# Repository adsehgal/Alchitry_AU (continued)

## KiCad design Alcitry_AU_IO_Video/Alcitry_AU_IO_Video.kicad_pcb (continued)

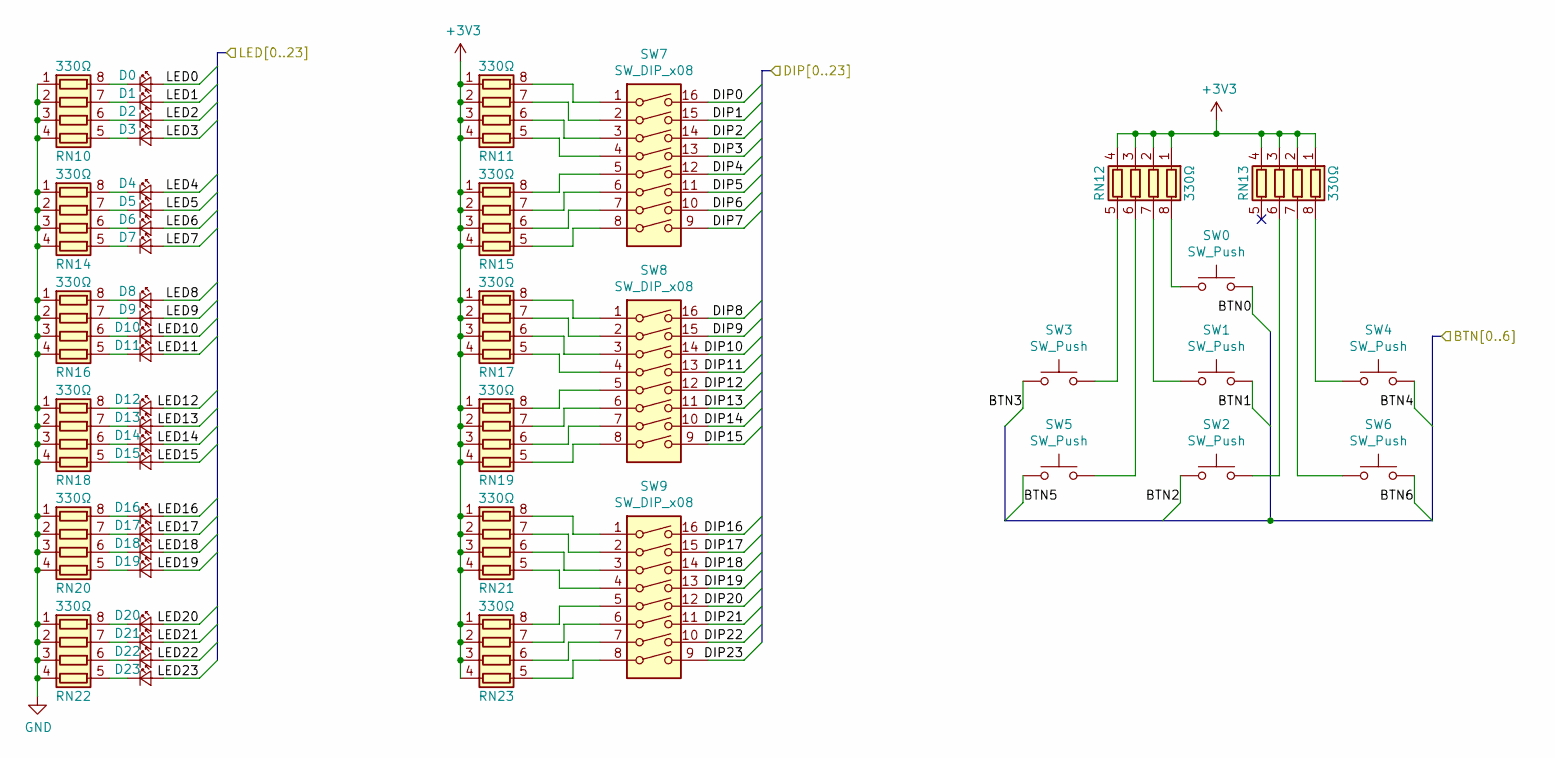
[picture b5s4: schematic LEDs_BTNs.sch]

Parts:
D0, D1, D2, D3, D4, D5, D6, D7, D8, D9, D10, D11, D12, D13, D14, D15, D16, D17, D18, D19, D20, D21, D22, D23: LED_Small; LED_0603_1608Metric_Pad1.05x0.95mm_HandSolder
RN10, RN11, RN12, RN13, RN14, RN15, RN16, RN17, RN18, RN19, RN20, RN21, RN22, RN23: 330Ω; R_Array_Convex_4x0603
SW0, SW1, SW2, SW3, SW4, SW5, SW6: SW_Push; SW_SPST_TL3342
SW7, SW8, SW9: SW_DIP_x08; SW_DIP_SPSTx08_Slide_Omron_A6H-8101_W6.15mm_P1.27mm

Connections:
+3V3: RN11.1 (R1.1), RN11.2 (R2.1), RN11.3 (R3.1), RN11.4 (R4.1), RN12.1 (R1.1), RN12.2 (R2.1), RN12.3 (R3.1), RN12.4 (R4.1), RN13.1 (R1.1), RN13.2 (R2.1), RN13.3 (R3.1), RN13.4 (R4.1), RN15.1 (R1.1), RN15.2 (R2.1), RN15.3 (R3.1), RN15.4 (R4.1), RN17.1 (R1.1), RN17.2 (R2.1), RN17.3 (R3.1), RN17.4 (R4.1), RN19.1 (R1.1), RN19.2 (R2.1), RN19.3 (R3.1), RN19.4 (R4.1), RN21.1 (R1.1), RN21.2 (R2.1), RN21.3 (R3.1), RN21.4 (R4.1), RN23.1 (R1.1), RN23.2 (R2.1), RN23.3 (R3.1), RN23.4 (R4.1); also elsewhere on the board
/BTN0: SW0.1; also elsewhere on the board
/BTN1: SW1.1; also elsewhere on the board
/BTN2: SW2.1; also elsewhere on the board
/BTN3: SW3.1; also elsewhere on the board
/BTN4: SW4.1; also elsewhere on the board
/BTN5: SW5.1; also elsewhere on the board
/BTN6: SW6.1; also elsewhere on the board
/DIP0: SW7.16; also elsewhere on the board
/DIP1: SW7.15; also elsewhere on the board
/DIP2: SW7.14; also elsewhere on the board
/DIP3: SW7.13; also elsewhere on the board
/DIP4: SW7.12; also elsewhere on the board
/DIP5: SW7.11; also elsewhere on the board
/DIP6: SW7.10; also elsewhere on the board
/DIP7: SW7.9; also elsewhere on the board
/DIP8: SW8.16; also elsewhere on the board
/DIP9: SW8.15; also elsewhere on the board
/DIP10: SW8.14; also elsewhere on the board
/DIP11: SW8.13; also elsewhere on the board
/DIP12: SW8.12; also elsewhere on the board
/DIP13: SW8.11; also elsewhere on the board
/DIP14: SW8.10; also elsewhere on the board
/DIP15: SW8.9; also elsewhere on the board
/DIP16: SW9.16; also elsewhere on the board
/DIP17: SW9.15; also elsewhere on the board
/DIP18: SW9.14; also elsewhere on the board
/DIP19: SW9.13; also elsewhere on the board
/DIP20: SW9.12; also elsewhere on the board
/DIP21: SW9.11; also elsewhere on the board
/DIP22: SW9.10; also elsewhere on the board
/DIP23: SW9.9; also elsewhere on the board
/LED0: D0.2 (A); also elsewhere on the board
/LED1: D1.2 (A); also elsewhere on the board
/LED2: D2.2 (A); also elsewhere on the board
/LED3: D3.2 (A); also elsewhere on the board
/LED4: D4.2 (A); also elsewhere on the board
/LED5: D5.2 (A); also elsewhere on the board
/LED6: D6.2 (A); also elsewhere on the board
/LED7: D7.2 (A); also elsewhere on the board
/LED8: D8.2 (A); also elsewhere on the board
/LED9: D9.2 (A); also elsewhere on the board
/LED10: D10.2 (A); also elsewhere on the board
/LED11: D11.2 (A); also elsewhere on the board
/LED12: D12.2 (A); also elsewhere on the board
/LED13: D13.2 (A); also elsewhere on the board
/LED14: D14.2 (A); also elsewhere on the board
/LED15: D15.2 (A); also elsewhere on the board
/LED16: D16.2 (A); also elsewhere on the board
/LED17: D17.2 (A); also elsewhere on the board
/LED18: D18.2 (A); also elsewhere on the board
/LED19: D19.2 (A); also elsewhere on the board
/LED20: D20.2 (A); also elsewhere on the board
/LED21: D21.2 (A); also elsewhere on the board
/LED22: D22.2 (A); also elsewhere on the board
/LED23: D23.2 (A); also elsewhere on the board
GND: RN10.1 (R1.1), RN10.2 (R2.1), RN10.3 (R3.1), RN10.4 (R4.1), RN14.1 (R1.1), RN14.2 (R2.1), RN14.3 (R3.1), RN14.4 (R4.1), RN16.1 (R1.1), RN16.2 (R2.1), RN16.3 (R3.1), RN16.4 (R4.1), RN18.1 (R1.1), RN18.2 (R2.1), RN18.3 (R3.1), RN18.4 (R4.1), RN20.1 (R1.1), RN20.2 (R2.1), RN20.3 (R3.1), RN20.4 (R4.1), RN22.1 (R1.1), RN22.2 (R2.1), RN22.3 (R3.1), RN22.4 (R4.1)
unnamed: D0.1 (K), RN10.8 (R1.2)
unnamed: D1.1 (K), RN10.7 (R2.2)
unnamed: D2.1 (K), RN10.6 (R3.2)
unnamed: D3.1 (K), RN10.5 (R4.2)
unnamed: D4.1 (K), RN14.8 (R1.2)
unnamed: D5.1 (K), RN14.7 (R2.2)
unnamed: D6.1 (K), RN14.6 (R3.2)
unnamed: D7.1 (K), RN14.5 (R4.2)
unnamed: D8.1 (K), RN16.8 (R1.2)
unnamed: D9.1 (K), RN16.7 (R2.2)
unnamed: D10.1 (K), RN16.6 (R3.2)
unnamed: D11.1 (K), RN16.5 (R4.2)
unnamed: D12.1 (K), RN18.8 (R1.2)
unnamed: D13.1 (K), RN18.7 (R2.2)
unnamed: D14.1 (K), RN18.6 (R3.2)
unnamed: D15.1 (K), RN18.5 (R4.2)
unnamed: D16.1 (K), RN20.8 (R1.2)
unnamed: D17.1 (K), RN20.7 (R2.2)
unnamed: D18.1 (K), RN20.6 (R3.2)
unnamed: D19.1 (K), RN20.5 (R4.2)
unnamed: D20.1 (K), RN22.8 (R1.2)
unnamed: D21.1 (K), RN22.7 (R2.2)
unnamed: D22.1 (K), RN22.6 (R3.2)
unnamed: D23.1 (K), RN22.5 (R4.2)
unnamed: RN11.5 (R4.2), SW7.4
unnamed: RN11.6 (R3.2), SW7.3
unnamed: RN11.7 (R2.2), SW7.2
unnamed: RN11.8 (R1.2), SW7.1
unnamed: RN12.5 (R4.2), SW3.2
unnamed: RN12.6 (R3.2), SW5.2
unnamed: RN12.7 (R2.2), SW1.2
unnamed: RN12.8 (R1.2), SW0.2
unnamed: RN13.6 (R3.2), SW2.2
unnamed: RN13.7 (R2.2), SW6.2
unnamed: RN13.8 (R1.2), SW4.2
unnamed: RN15.5 (R4.2), SW7.8
unnamed: RN15.6 (R3.2), SW7.7
unnamed: RN15.7 (R2.2), SW7.6
unnamed: RN15.8 (R1.2), SW7.5
unnamed: RN17.5 (R4.2), SW8.4
unnamed: RN17.6 (R3.2), SW8.3
unnamed: RN17.7 (R2.2), SW8.2
unnamed: RN17.8 (R1.2), SW8.1
unnamed: RN19.5 (R4.2), SW8.8
unnamed: RN19.6 (R3.2), SW8.7
unnamed: RN19.7 (R2.2), SW8.6
unnamed: RN19.8 (R1.2), SW8.5
unnamed: RN21.5 (R4.2), SW9.4
unnamed: RN21.6 (R3.2), SW9.3
unnamed: RN21.7 (R2.2), SW9.2
unnamed: RN21.8 (R1.2), SW9.1
unnamed: RN23.5 (R4.2), SW9.8
unnamed: RN23.6 (R3.2), SW9.7
unnamed: RN23.7 (R2.2), SW9.6
unnamed: RN23.8 (R1.2), SW9.5

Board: 2 copper layers, 90 parts (16 on the bottom side), 201 nets, no tracks yet.

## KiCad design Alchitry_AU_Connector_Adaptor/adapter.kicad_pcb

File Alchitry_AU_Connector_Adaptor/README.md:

# Alchitry_AU_Adaptor
Adaptor designed to convert the Alchitry AU 0.5mm pitch connectors to a more manageable 1mm pitch connectors offered by Harwin.

Goal of this adaptor is to make breakout boards much easier to solder once the adaptor is in place.

Harwin Connectors:

Female: M55-7005042R

      https://www.digikey.com/product-detail/en/harwin-inc/M55-7005042R/952-3872-1-ND/8537656
      
Male: M55-6005042R

      https://www.digikey.com/product-detail/en/harwin-inc/M55-6005042R/952-3840-1-ND/8537624

The prototype boards were fabricated by JLCPCB.

EDA tool used: KiCad

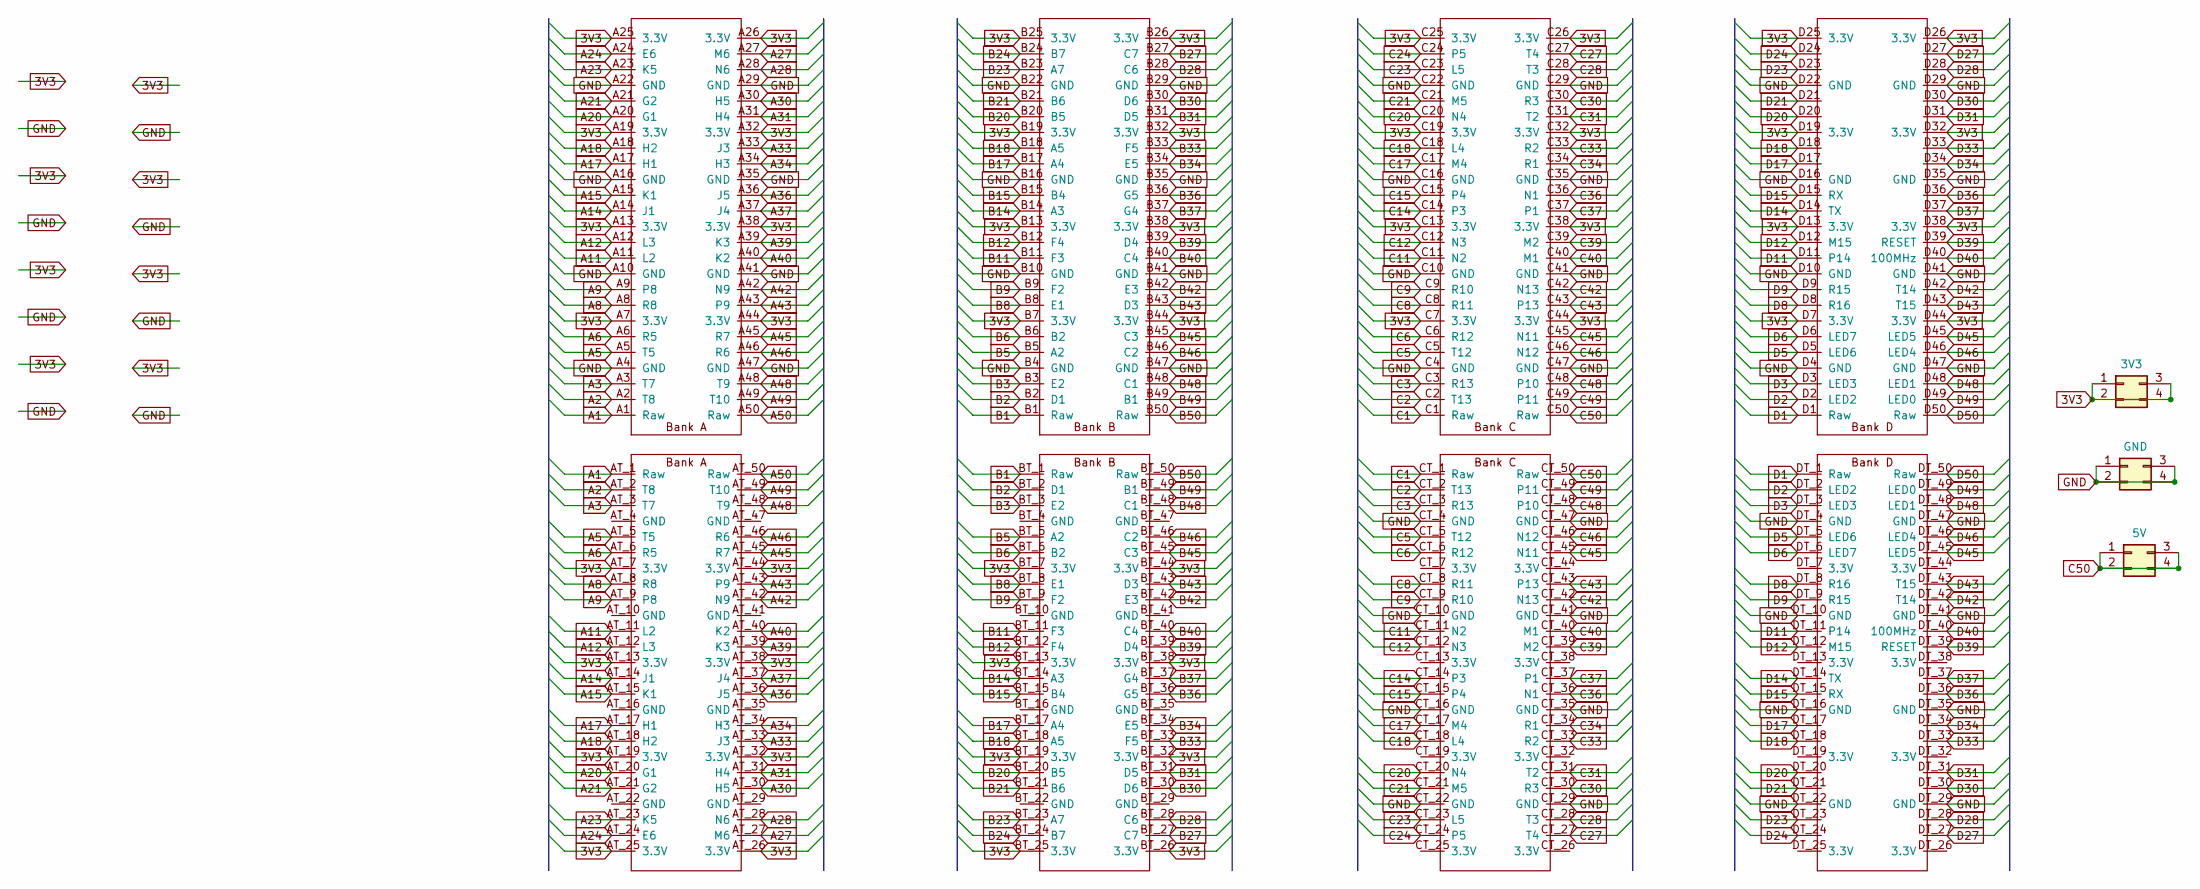
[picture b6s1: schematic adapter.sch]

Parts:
J1: 3V3; PinHeader_2x02_P2.54mm_Vertical
J2: GND; PinHeader_2x02_P2.54mm_Vertical
J3: 5V; PinHeader_2x02_P2.54mm_Vertical
U1: ADAPTOR_TOPX4; Alchitry_board_ADAPTOR_TOP

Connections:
3V3: J1.1, J1.2, J1.3, J1.4, U1.A7 (3.3V), U1.A13 (3.3V), U1.A19 (3.3V), U1.A25 (3.3V), U1.A26 (3.3V), U1.A32 (3.3V), U1.A38 (3.3V), U1.A44 (3.3V), U1.AT_7 (3.3V), U1.AT_13 (3.3V), U1.AT_19 (3.3V), U1.AT_25 (3.3V), U1.AT_26 (3.3V), U1.AT_32 (3.3V), U1.AT_38 (3.3V), U1.AT_44 (3.3V), U1.B7 (3.3V), U1.B13 (3.3V), U1.B19 (3.3V), U1.B25 (3.3V), U1.B26 (3.3V), U1.B32 (3.3V), U1.B38 (3.3V), U1.B44 (3.3V), U1.BT_7 (3.3V), U1.BT_13 (3.3V), U1.BT_19 (3.3V), U1.BT_25 (3.3V), U1.BT_26 (3.3V), U1.BT_32 (3.3V), U1.BT_38 (3.3V), U1.BT_44 (3.3V), U1.C7 (3.3V), U1.C13 (3.3V), U1.C19 (3.3V), U1.C25 (3.3V), U1.C26 (3.3V), U1.C32 (3.3V), U1.C38 (3.3V), U1.C44 (3.3V), U1.D7 (3.3V), U1.D13 (3.3V), U1.D19 (3.3V), U1.D25 (3.3V), U1.D26 (3.3V), U1.D32 (3.3V), U1.D38 (3.3V), U1.D44 (3.3V)
A1: U1.A1 (Raw), U1.AT_1 (Raw)
A2: U1.A2 (T8), U1.AT_2 (T8)
A3: U1.A3 (T7), U1.AT_3 (T7)
A5: U1.A5 (T5), U1.AT_5 (T5)
A6: U1.A6 (R5), U1.AT_6 (R5)
A8: U1.A8 (R8), U1.AT_8 (R8)
A9: U1.A9 (P8), U1.AT_9 (P8)
A11: U1.A11 (L2), U1.AT_11 (L2)
A12: U1.A12 (L3), U1.AT_12 (L3)
A14: U1.A14 (J1), U1.AT_14 (J1)
A15: U1.A15 (K1), U1.AT_15 (K1)
A17: U1.A17 (H1), U1.AT_17 (H1)
A18: U1.A18 (H2), U1.AT_18 (H2)
A20: U1.A20 (G1), U1.AT_20 (G1)
A21: U1.A21 (G2), U1.AT_21 (G2)
A23: U1.A23 (K5), U1.AT_23 (K5)
A24: U1.A24 (E6), U1.AT_24 (E6)
A27: U1.A27 (M6), U1.AT_27 (M6)
A28: U1.A28 (N6), U1.AT_28 (N6)
A30: U1.A30 (H5), U1.AT_30 (H5)
A31: U1.A31 (H4), U1.AT_31 (H4)
A33: U1.A33 (J3), U1.AT_33 (J3)
A34: U1.A34 (H3), U1.AT_34 (H3)
A36: U1.A36 (J5), U1.AT_36 (J5)
A37: U1.A37 (J4), U1.AT_37 (J4)
A39: U1.A39 (K3), U1.AT_39 (K3)
A40: U1.A40 (K2), U1.AT_40 (K2)
A42: U1.A42 (N9), U1.AT_42 (N9)
A43: U1.A43 (P9), U1.AT_43 (P9)
A45: U1.A45 (R7), U1.AT_45 (R7)
A46: U1.A46 (R6), U1.AT_46 (R6)
A48: U1.A48 (T9), U1.AT_48 (T9)
A49: U1.A49 (T10), U1.AT_49 (T10)
A50: U1.A50 (Raw), U1.AT_50 (Raw)
B1: U1.B1 (Raw), U1.BT_1 (Raw)
B2: U1.B2 (D1), U1.BT_2 (D1)
B3: U1.B3 (E2), U1.BT_3 (E2)
B5: U1.B5 (A2), U1.BT_5 (A2)
B6: U1.B6 (B2), U1.BT_6 (B2)
B8: U1.B8 (E1), U1.BT_8 (E1)
B9: U1.B9 (F2), U1.BT_9 (F2)
B11: U1.B11 (F3), U1.BT_11 (F3)
B12: U1.B12 (F4), U1.BT_12 (F4)
B14: U1.B14 (A3), U1.BT_14 (A3)
B15: U1.B15 (B4), U1.BT_15 (B4)
B17: U1.B17 (A4), U1.BT_17 (A4)
B18: U1.B18 (A5), U1.BT_18 (A5)
B20: U1.B20 (B5), U1.BT_20 (B5)
B21: U1.B21 (B6), U1.BT_21 (B6)
B23: U1.B23 (A7), U1.BT_23 (A7)
B24: U1.B24 (B7), U1.BT_24 (B7)
B27: U1.B27 (C7), U1.BT_27 (C7)
B28: U1.B28 (C6), U1.BT_28 (C6)
B30: U1.B30 (D6), U1.BT_30 (D6)
B31: U1.B31 (D5), U1.BT_31 (D5)
B33: U1.B33 (F5), U1.BT_33 (F5)
B34: U1.B34 (E5), U1.BT_34 (E5)
B36: U1.B36 (G5), U1.BT_36 (G5)
B37: U1.B37 (G4), U1.BT_37 (G4)
B39: U1.B39 (D4), U1.BT_39 (D4)
B40: U1.B40 (C4), U1.BT_40 (C4)
B42: U1.B42 (E3), U1.BT_42 (E3)
B43: U1.B43 (D3), U1.BT_43 (D3)
B45: U1.B45 (C3), U1.BT_45 (C3)
B46: U1.B46 (C2), U1.BT_46 (C2)
B48: U1.B48 (C1), U1.BT_48 (C1)
B49: U1.B49 (B1), U1.BT_49 (B1)
B50: U1.B50 (Raw), U1.BT_50 (Raw)
C1: U1.C1 (Raw), U1.CT_1 (Raw)
C2: U1.C2 (T13), U1.CT_2 (T13)
C3: U1.C3 (R13), U1.CT_3 (R13)
C5: U1.C5 (T12), U1.CT_5 (T12)
C6: U1.C6 (R12), U1.CT_6 (R12)
C8: U1.C8 (R11), U1.CT_8 (R11)
C9: U1.C9 (R10), U1.CT_9 (R10)
C11: U1.C11 (N2), U1.CT_11 (N2)
C12: U1.C12 (N3), U1.CT_12 (N3)
C14: U1.C14 (P3), U1.CT_14 (P3)
C15: U1.C15 (P4), U1.CT_15 (P4)
C17: U1.C17 (M4), U1.CT_17 (M4)
C18: U1.C18 (L4), U1.CT_18 (L4)
C20: U1.C20 (N4), U1.CT_20 (N4)
C21: U1.C21 (M5), U1.CT_21 (M5)
C23: U1.C23 (L5), U1.CT_23 (L5)
C24: U1.C24 (P5), U1.CT_24 (P5)
C27: U1.C27 (T4), U1.CT_27 (T4)
C28: U1.C28 (T3), U1.CT_28 (T3)
C30: U1.C30 (R3), U1.CT_30 (R3)
C31: U1.C31 (T2), U1.CT_31 (T2)
C33: U1.C33 (R2), U1.CT_33 (R2)
C34: U1.C34 (R1), U1.CT_34 (R1)
C36: U1.C36 (N1), U1.CT_36 (N1)
C37: U1.C37 (P1), U1.CT_37 (P1)
C39: U1.C39 (M2), U1.CT_39 (M2)
C40: U1.C40 (M1), U1.CT_40 (M1)
C42: U1.C42 (N13), U1.CT_42 (N13)
C43: U1.C43 (P13), U1.CT_43 (P13)
C45: U1.C45 (N11), U1.CT_45 (N11)
C46: U1.C46 (N12), U1.CT_46 (N12)
C48: U1.C48 (P10), U1.CT_48 (P10)
C49: U1.C49 (P11), U1.CT_49 (P11)
C50: J3.1, J3.2, J3.3, J3.4, U1.C50 (Raw), U1.CT_50 (Raw)
D1: U1.D1 (Raw), U1.DT_1 (Raw)
D2: U1.D2 (LED2), U1.DT_2 (LED2)
D3: U1.D3 (LED3), U1.DT_3 (LED3)
D5: U1.D5 (LED6), U1.DT_5 (LED6)
D6: U1.D6 (LED7), U1.DT_6 (LED7)
D8: U1.D8 (R16), U1.DT_8 (R16)
D9: U1.D9 (R15), U1.DT_9 (R15)
D11: U1.D11 (P14), U1.DT_11 (P14)
D12: U1.D12 (M15), U1.DT_12 (M15)
D14: U1.D14 (TX), U1.DT_14 (TX)
D15: U1.D15 (RX), U1.DT_15 (RX)
D17: U1.D17, U1.DT_17
D18: U1.D18, U1.DT_18
D20: U1.D20, U1.DT_20
D21: U1.D21, U1.DT_21
D23: U1.D23, U1.DT_23
D24: U1.D24, U1.DT_24
D27: U1.D27, U1.DT_27
D28: U1.D28, U1.DT_28
D30: U1.D30, U1.DT_30
D31: U1.D31, U1.DT_31
D33: U1.D33, U1.DT_33
D34: U1.D34, U1.DT_34
D36: U1.D36, U1.DT_36
D37: U1.D37, U1.DT_37
D39: U1.D39 (RESET), U1.DT_39 (RESET)
D40: U1.D40 (100MHz), U1.DT_40 (100MHz)
D42: U1.D42 (T14), U1.DT_42 (T14)
D43: U1.D43 (T15), U1.DT_43 (T15)
D45: U1.D45 (LED5), U1.DT_45 (LED5)
D46: U1.D46 (LED4), U1.DT_46 (LED4)
D48: U1.D48 (LED1), U1.DT_48 (LED1)
D49: U1.D49 (LED0), U1.DT_49 (LED0)
D50: U1.D50 (Raw), U1.DT_50 (Raw)
GND: J2.1, J2.2, J2.3, J2.4, U1.A4 (GND), U1.A10 (GND), U1.A16 (GND), U1.A22 (GND), U1.A29 (GND), U1.A35 (GND), U1.A41 (GND), U1.A47 (GND), U1.B4 (GND), U1.B10 (GND), U1.B16 (GND), U1.B22 (GND), U1.B29 (GND), U1.B35 (GND), U1.B41 (GND), U1.B47 (GND), U1.C4 (GND), U1.C10 (GND), U1.C16 (GND), U1.C22 (GND), U1.C29 (GND), U1.C35 (GND), U1.C41 (GND), U1.C47 (GND), U1.CT_4 (GND), U1.CT_10 (GND), U1.CT_16 (GND), U1.CT_22 (GND), U1.CT_29 (GND), U1.CT_35 (GND), U1.CT_41 (GND), U1.CT_47 (GND), U1.D4 (GND), U1.D10 (GND), U1.D16 (GND), U1.D22 (GND), U1.D29 (GND), U1.D35 (GND), U1.D41 (GND), U1.D47 (GND), U1.DT_4 (GND), U1.DT_10 (GND), U1.DT_16 (GND), U1.DT_22 (GND), U1.DT_29 (GND), U1.DT_35 (GND), U1.DT_41 (GND), U1.DT_47 (GND)

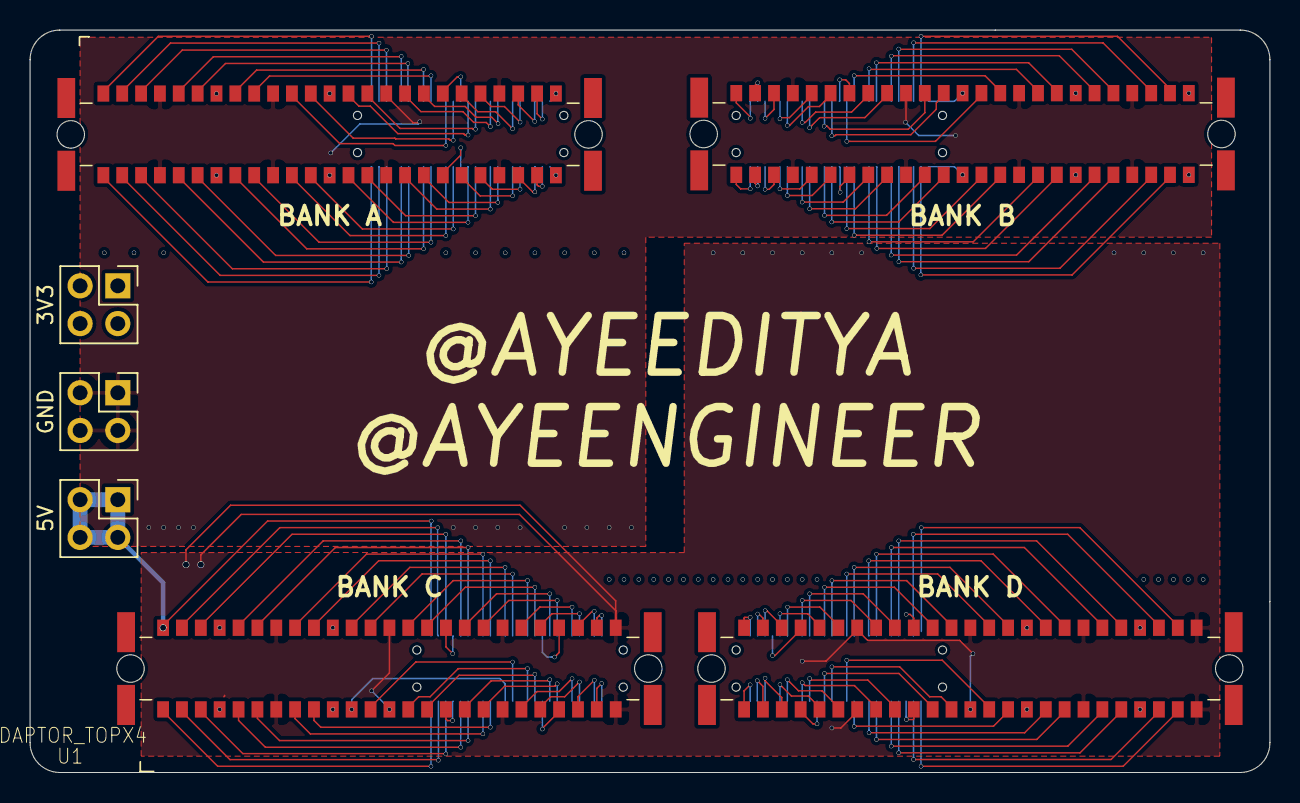
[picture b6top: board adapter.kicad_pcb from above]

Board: 2 copper layers, 83.5 x 50.0 mm, 4 parts (0 on the bottom side), 138 nets.

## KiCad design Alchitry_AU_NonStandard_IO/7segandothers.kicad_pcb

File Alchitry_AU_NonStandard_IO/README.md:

# Alchitry_AU_BreakoutV2
Breakout Board designed to be used with the Alchitry AU FPGA in conjunction with the mezzanine adaptor dersigned by me.
The breakout board has 5x tacticle buttons, 8x LEDs, 4x DIP switches, 2x 2-Digit 7 segment displays, extra breakout pins from Bank B as well as pin headers for the HDMI adaptor designed by 1bit-squared.

Goal of this breakout board is to offer similar functionality as the one offered by Alchitry in addition to HDMI output and extra headers if needed.

Note: the HDMI headers can be used as regular I/O as well.

HDMI Adaptor:

https://1bitsquared.com/products/pmod-digital-video-interface?variant=11770730020911&currency=USD&gclid=Cj0KCQjwov3nBRDFARIsANgsdoHOZecOSm0TIER7f1FJA3ifWDU8KhmRx257o6HcA4yRRT3OkXDNP8oaArPeEALw_wcB

DIP Switch:

https://lcsc.com/product-detail/DIP-Switches_Cixi-Tonver-Elec-Cixi-Tonver-Elec-HAD-04H-R_C3693.html

LEDs:

https://lcsc.com/product-detail/Light-Emitting-Diodes-LED_0805-blue_C205441.html

Tactile Buttons:

https://lcsc.com/product-detail/Tactile-Switches_Korean-Hroparts-Elec-K2-1187SQ-A4SW-06_C92584.html

7 Segment Displays:

https://lcsc.com/product-detail/Led-Segment-Display_SUNLIGHT-SLS0392FB4A1GD_C226000.html

Pull Down Resistors:

https://lcsc.com/product-detail/New-Arrivals_SANYEAR-SYLE0805JN330RP_C385915.html

Harwin Connectors:

Female: M55-7005042R

  https://www.digikey.com/product-detail/en/harwin-inc/M55-7005042R/952-3872-1-ND/8537656
Male: M55-6005042R

  https://www.digikey.com/product-detail/en/harwin-inc/M55-6005042R/952-3840-1-ND/8537624
  
The prototype boards were fabricated by JLCPCB.

EDA tool used: KiCad

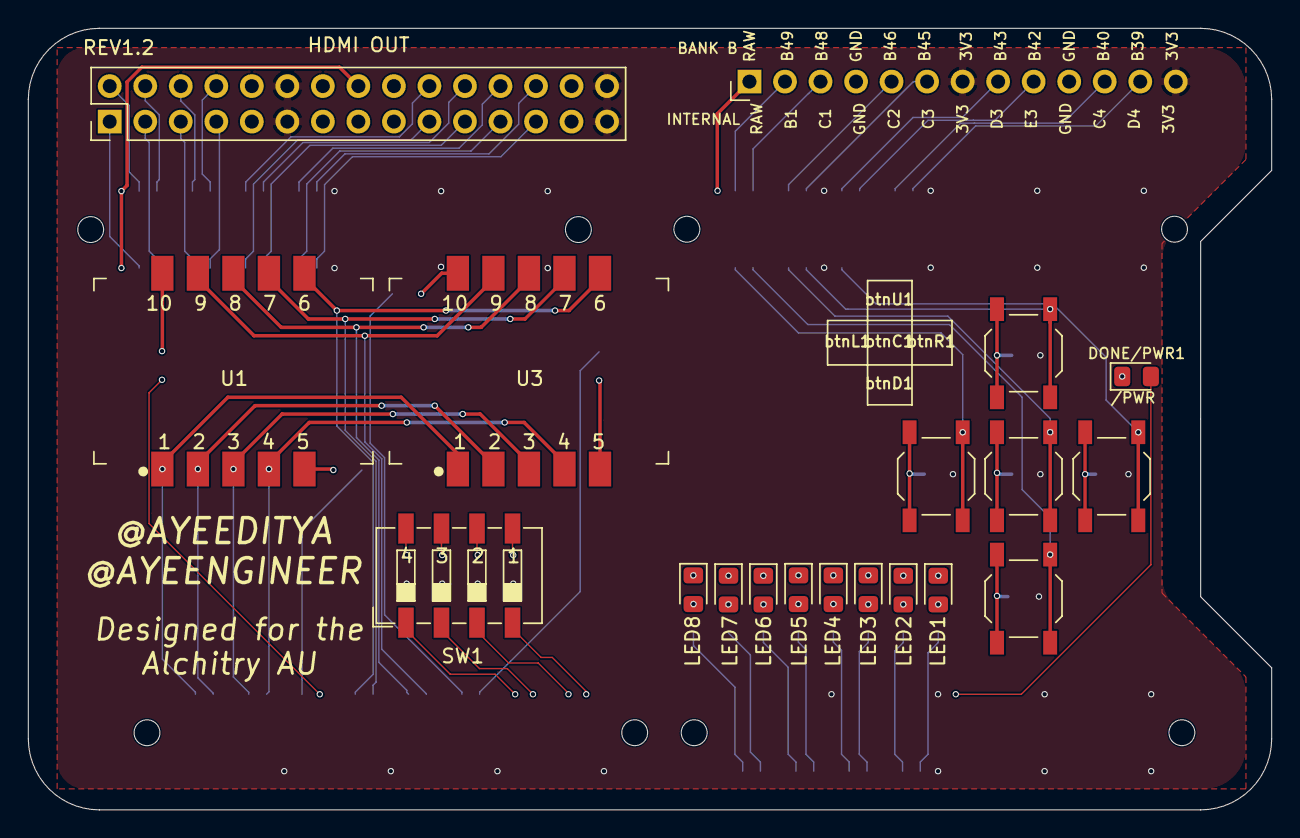
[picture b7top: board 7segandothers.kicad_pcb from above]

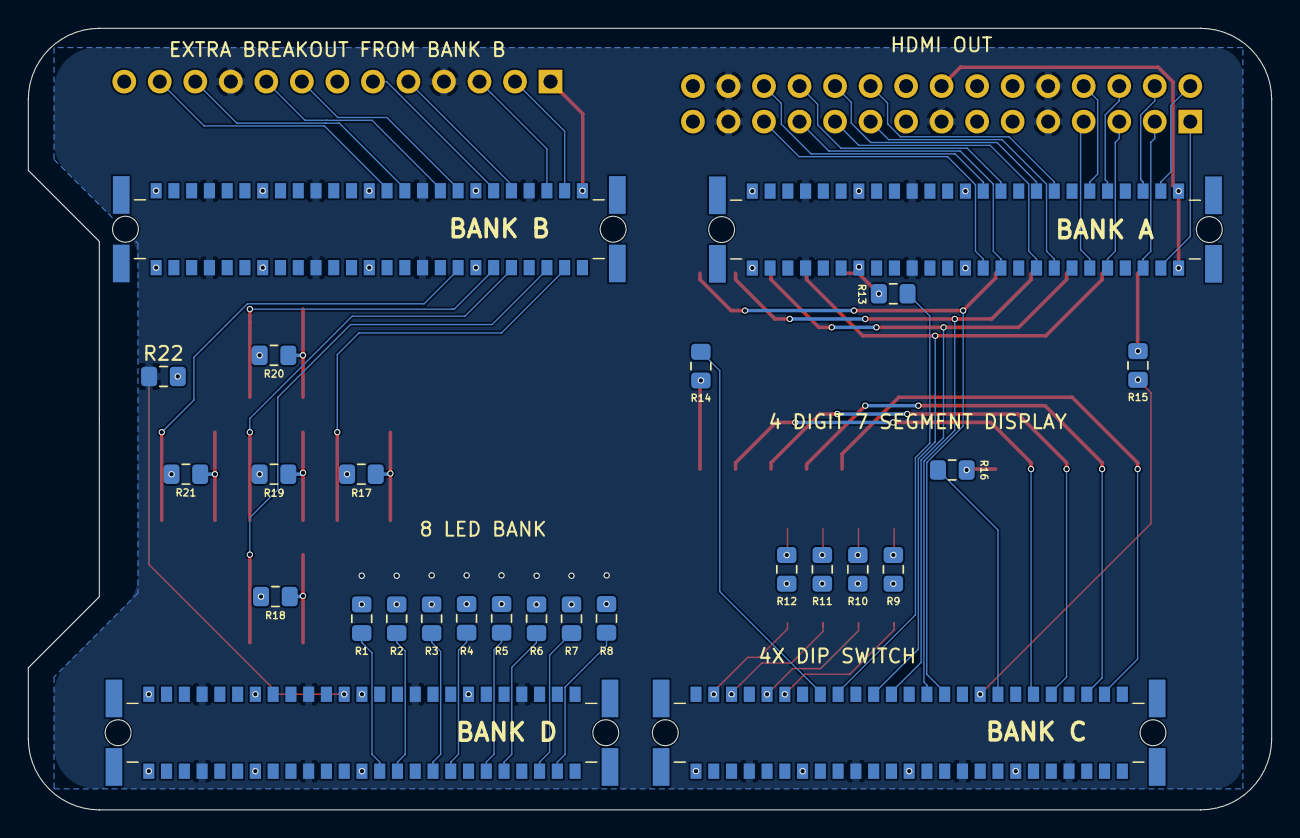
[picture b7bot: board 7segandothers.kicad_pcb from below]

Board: 2 copper layers, 88.9 x 55.9 mm, 42 parts (22 on the bottom side), 80 nets.

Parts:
DONE/PWR1: LED; LED_0805_2012Metric_Pad1.15x1.40mm_HandSolder
J1: Conn_02x15_Counter_Clockwise; PinHeader_2x15_P2.54mm_Vertical
J2: Conn_01x13_Male; PinHeader_1x13_P2.54mm_Vertical
LED1, LED2, LED3, LED4, LED5, LED6, LED7, LED8: LED; LED_0805_2012Metric_Pad1.15x1.40mm_HandSolder
R1, R2, R3, R4, R5, R6, R7, R8, R9, R10, R11, R12, R13, R14, R15, R16, R17, R18, R19, R20, R21, R22: R_Small_US; R_0805_2012Metric_Pad1.15x1.40mm_HandSolder
SW1: SW_DIP_x04; SW_DIP_SPSTx04_Slide_6.7x11.72mm_W6.73mm_P2.54mm_LowProfile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
U1, U3: smd_7seg_2dig_SLS0392FB4A1GD
U2: boardmezzanine_new; Alchitry_board_adapter_btm
btnC1: SW_Push_Dual; SW_SPST_TL3342
btnD1: SW_Push_Dual; SW_SPST_TL3342
btnL1: SW_Push_Dual; SW_SPST_TL3342
btnR1: SW_Push_Dual; SW_SPST_TL3342
btnU1: SW_Push_Dual; SW_SPST_TL3342

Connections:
B0: J1.19, U2.A40
B1: J1.11, U2.A9
B2: J1.10, U2.A8
B3: J1.21, U2.A43
CK: J1.20, U2.A42
DE: J1.12, U2.A11
G0: J1.4, U2.A6
G1: J1.27, U2.A45
G2: J1.3, U2.A5
G3: J1.28, U2.A46
GNDREF: J1.5, J1.8, J1.14, J1.17, J1.26, J2.4, J2.10, LED1.1, LED2.1, LED3.1, LED4.1, LED5.1, LED6.1, LED7.1, LED8.1, R22.1, U2.A16, U2.A22, U2.A29, U2.A35, U2.B10, U2.B16, U2.B22, U2.B29, U2.B35, U2.B41, U2.B47, U2.C4, U2.C10, U2.C16, U2.C22, U2.D16, U2.D22, U2.D29, U2.D35, U2.D41, U2.D47
HS: J1.18, U2.A39
unnamed: DONE/PWR1.1, R22.2
unnamed: DONE/PWR1.2, U2.D37
unnamed: J2.1, U2.B50
unnamed: J2.2, U2.B49
unnamed: J2.3, U2.B48
unnamed: J2.5, U2.B46
unnamed: J2.6, U2.B45
unnamed: J2.8, U2.B43
unnamed: J2.9, U2.B42
unnamed: J2.11, U2.B40
unnamed: J2.12, U2.B39
unnamed: LED1.2, R1.1
unnamed: LED2.2, R2.1
unnamed: LED3.2, R3.1
unnamed: LED4.2, R4.1
unnamed: LED5.2, R5.1
unnamed: LED6.2, R6.1
unnamed: LED7.2, R7.1
unnamed: LED8.2, R8.1
unnamed: R1.2, U2.D12
unnamed: R2.2, U2.D11
unnamed: R3.2, U2.D9
unnamed: R4.2, U2.D8
unnamed: R5.2, U2.D6
unnamed: R6.2, U2.D5
unnamed: R7.2, U2.D3
unnamed: R8.2, U2.D2
unnamed: R9.2, SW1.8
unnamed: R10.2, SW1.7
unnamed: R11.2, SW1.6
unnamed: R12.2, SW1.5
unnamed: R13.1, U2.C34
unnamed: R13.2, U3.10
unnamed: R14.1, U3.5
unnamed: R14.2, U2.C33
unnamed: R15.1, U2.C42
unnamed: R15.2, U1.10
unnamed: R16.1, U1.5
unnamed: R16.2, U2.C43
unnamed: R17.1, btnL1.1
unnamed: R18.1, btnD1.1
unnamed: R19.1, btnC1.1
unnamed: R20.1, btnU1.1
unnamed: R21.1, btnR1.1
unnamed: SW1.1, U2.C31
unnamed: SW1.2, U2.C30
unnamed: SW1.3, U2.C28
unnamed: SW1.4, U2.C27
unnamed: U1.1, U2.C49, U3.1
unnamed: U1.2, U2.C48, U3.2
unnamed: U1.3, U2.C46, U3.3
unnamed: U1.4, U2.C45, U3.4
unnamed: U1.6, U2.C40, U3.6
unnamed: U1.7, U2.C39, U3.7
unnamed: U1.8, U2.C37, U3.8
unnamed: U1.9, U2.C36, U3.9
unnamed: U2.B2, btnL1.2
unnamed: U2.B3, btnD1.2
unnamed: U2.B5, btnC1.2
unnamed: U2.B6, btnU1.2
unnamed: U2.B8, btnR1.2
R0: J1.2, U2.A3
R1: J1.29, U2.A48
R2: J1.1, U2.A2
R3: J1.30, U2.A49
RAW: J1.23, U2.A1, U2.A50
VCC: J1.6, J1.15, J1.16, J1.25, J2.7, J2.13, R9.1, R10.1, R11.1, R12.1, R17.2, R18.2, R19.2, R20.2, R21.2, U2.A13, U2.A19, U2.A25, U2.A26, U2.A32, U2.A38, U2.B7, U2.B13, U2.B19, U2.B25, U2.B26, U2.B32, U2.B38, U2.B44, U2.C7, U2.C13, U2.C19, U2.C25, U2.D13, U2.D19, U2.D25, U2.D26, U2.D32, U2.D38, U2.D44
VS: J1.13, U2.A12

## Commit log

2020-02-12 Gerber and schematic added
2020-03-20 Removed redundancies
2020-03-30 Sorted repo
2020-03-30 Repo formatted
2020-04-10 Repo readme updated
2020-04-10 Repo updated - ignore
2020-04-10 Readme updates
2020-04-27 both shift not working
2020-05-12 update to shield
2020-05-12 v3 made
2020-05-26 Updated HDMI shield schematic
2020-06-05 removed islands
2020-06-19 Generated gerber files and organized into subfolders
2020-06-26 LOGO ADDED
2020-07-27 Starting a play shield layout
2020-07-30 grouped footprints by function
2020-08-10 minor changes
2020-08-21 started new shield
2020-08-22 replaced 7segs with custom footprints
2020-08-22 laid out switches, btns and leds
2020-08-24 adding USB C for OTG programming and serial
2020-09-04 updated shield v4 schematic
2020-09-04 reorganized folder
2020-09-04 relocated HDMI and output all files
2020-09-04 removed old project
2020-09-05 organized files
2020-09-22 created panelized gerbers
2020-09-22 added gerber zip
2020-09-22 gerber update
2020-09-27 fixed dirll sizes
2020-12-17 kicad updates
2020-12-26 readme update
2020-12-26 v2 led half
2020-12-27 working on placement
2020-12-27 switches and 7seg routed
2020-12-27 routing complete... ,maybe add button
2020-12-29 layout again
2020-12-29 added push butttons
2021-01-31 led matrix init
